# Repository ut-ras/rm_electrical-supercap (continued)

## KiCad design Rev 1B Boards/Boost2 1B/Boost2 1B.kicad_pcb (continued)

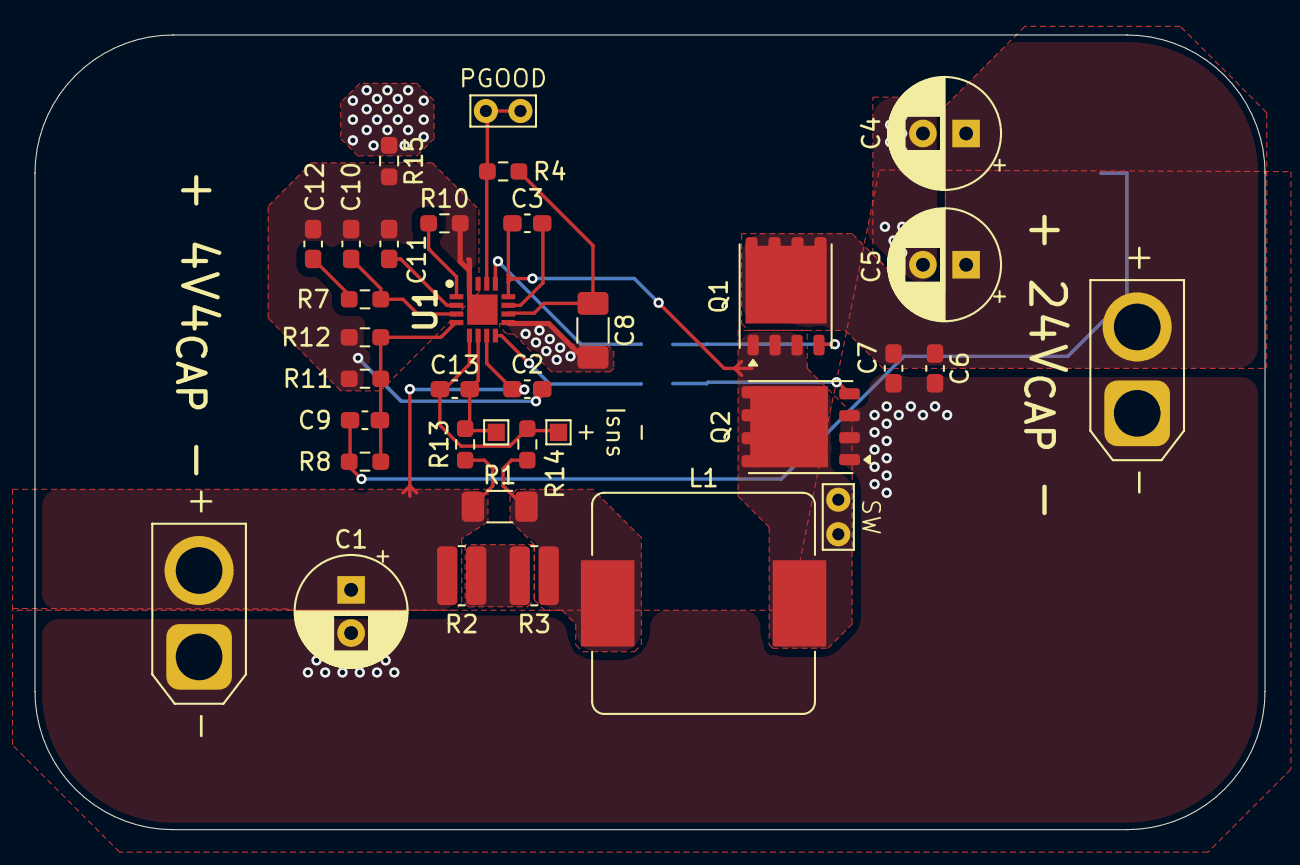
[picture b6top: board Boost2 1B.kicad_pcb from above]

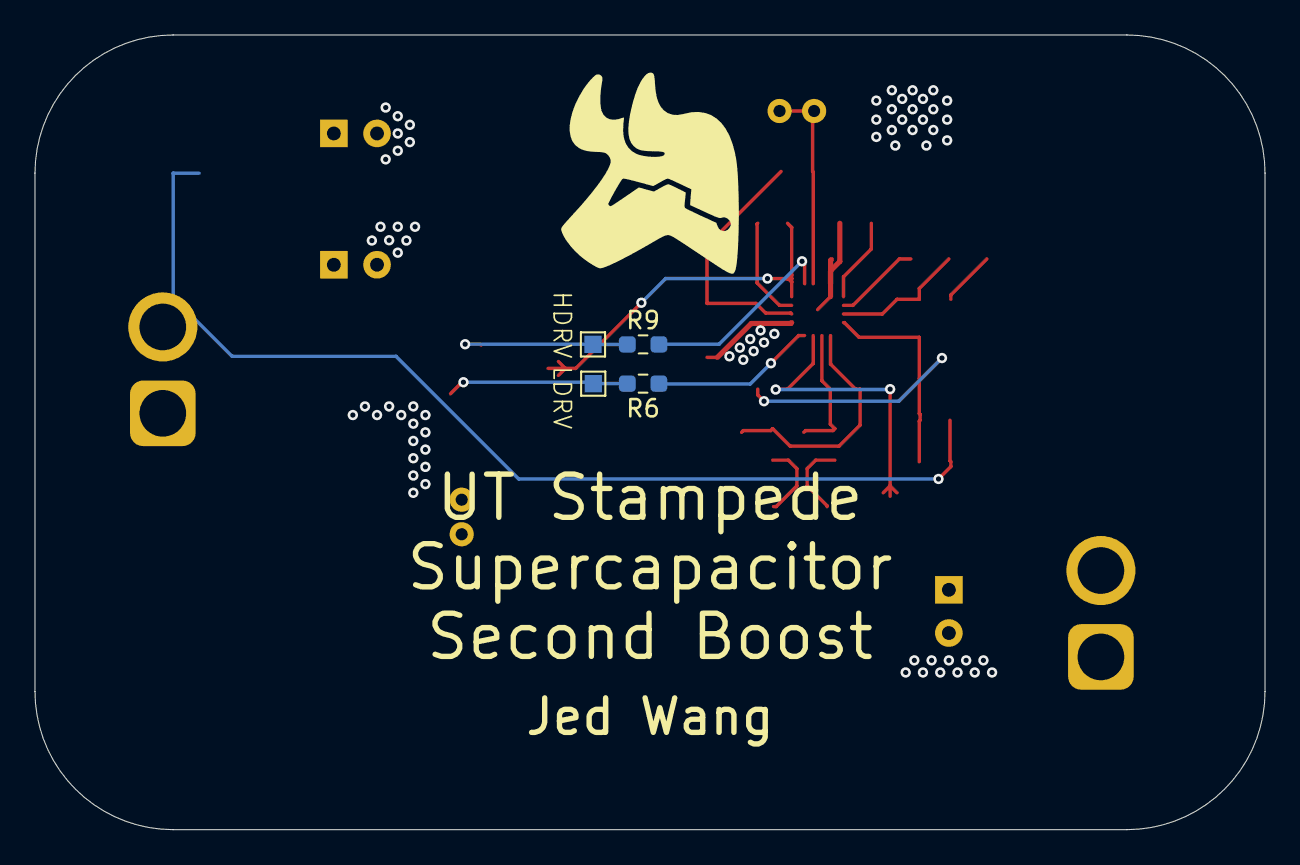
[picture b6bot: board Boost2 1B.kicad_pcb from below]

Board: 4 copper layers, 71.2 x 46.0 mm, 39 parts (4 on the bottom side), 21 nets.

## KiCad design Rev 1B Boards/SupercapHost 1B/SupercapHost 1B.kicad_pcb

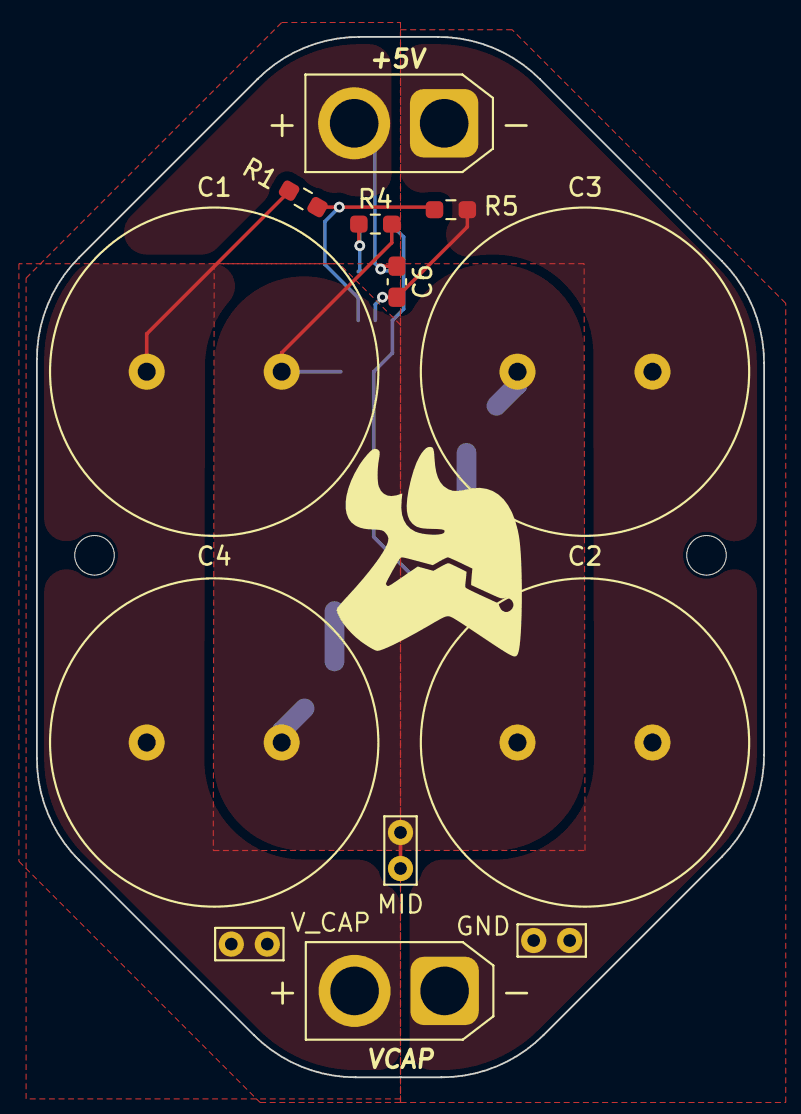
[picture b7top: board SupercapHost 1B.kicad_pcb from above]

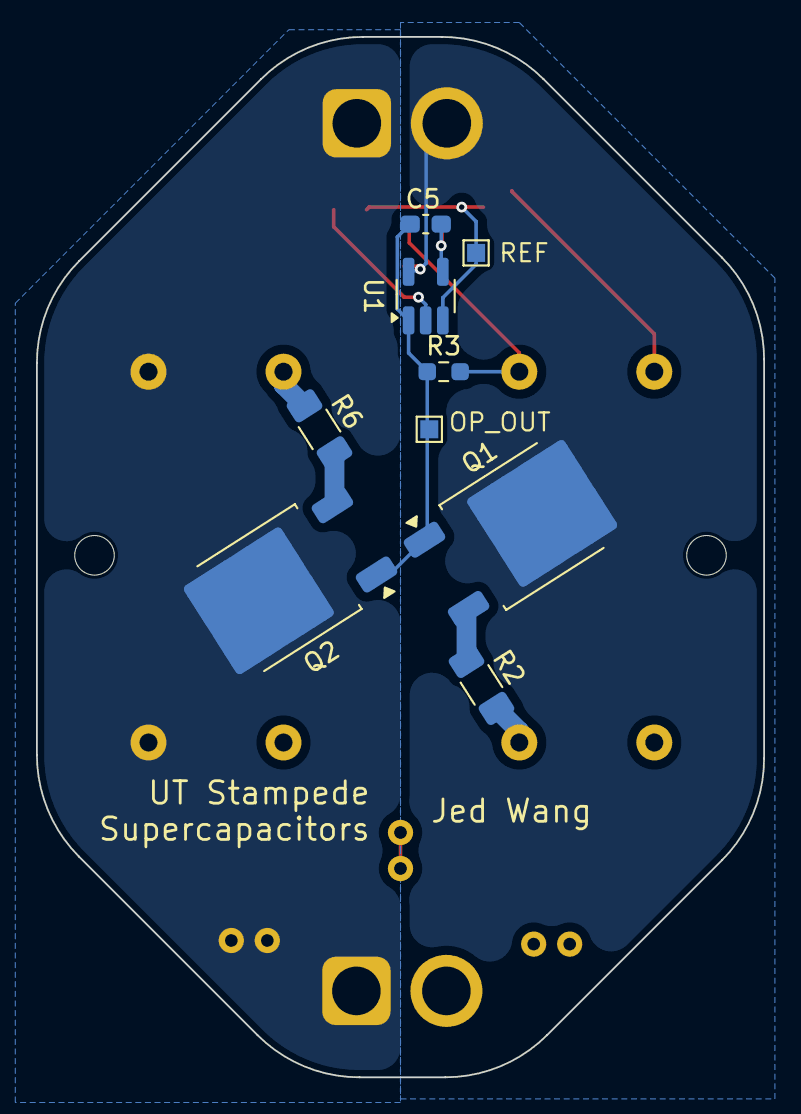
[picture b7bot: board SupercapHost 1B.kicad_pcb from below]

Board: 2 copper layers, 40.4 x 57.8 mm, 22 parts (9 on the bottom side), 9 nets.

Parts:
C1, C2, C3, C4: 110; C_Radial_D18.0mm_H35.5mm_P7.50mm
C5: 100p; C_0603_1608Metric_Pad1.08x0.95mm_HandSolder
C6: 0.1u; C_0603_1608Metric_Pad1.08x0.95mm_HandSolder
J1, J2: XT30_F; AMASS_XT30U-F_1x02_P5.0mm_Vertical
Q1: 2SCR587D3; TO-252-2
Q2: 2SAR587D3; TO-252-2
R1, R5: 1Meg; R_0603_1608Metric_Pad0.98x0.95mm_HandSolder
R2, R6: 0.1; R_1206_3216Metric_Pad1.30x1.75mm_HandSolder
R3, R4: 100; R_0603_1608Metric_Pad0.98x0.95mm_HandSolder
TP1, TP4: TP; TestPoint_Pad_1.0x1.0mm
TP2, TP3, TP5: TP; TestPoint_Bridge_Pitch2.0mm_Drill0.7mm
U1: TLV9301xDBV; SOT-23-5_HandSoldering

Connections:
/Supercapacitors/LOWER_R: Q2.3 (E), R6.2
/Supercapacitors/MID: C1.2, C2.2, C3.1, C4.1, R2.2, R3.2, R4.1, R6.1, TP3.1
/Supercapacitors/OP_OUT: C5.2, Q1.1 (B), Q2.1 (B), R3.1, TP1.1, U1.1
/Supercapacitors/REF: R1.2, R5.1, TP4.1, U1.3 (+)
/Supercapacitors/UPPER_R: Q1.3 (E), R2.1
/Supercapacitors/V-: C5.1, R4.2, U1.4 (-)
/Supercapacitors/V_{CAP}: C1.1, C2.1, J1.2, R1.1, TP2.1
/Supercapacitors/V_{CC}: C6.1, J2.2, Q1.2 (C), U1.5 (V+)
GND1: C3.2, C4.2, C6.2, J1.1, J2.1, Q2.2 (C), R5.2, TP5.1, U1.2 (V-)

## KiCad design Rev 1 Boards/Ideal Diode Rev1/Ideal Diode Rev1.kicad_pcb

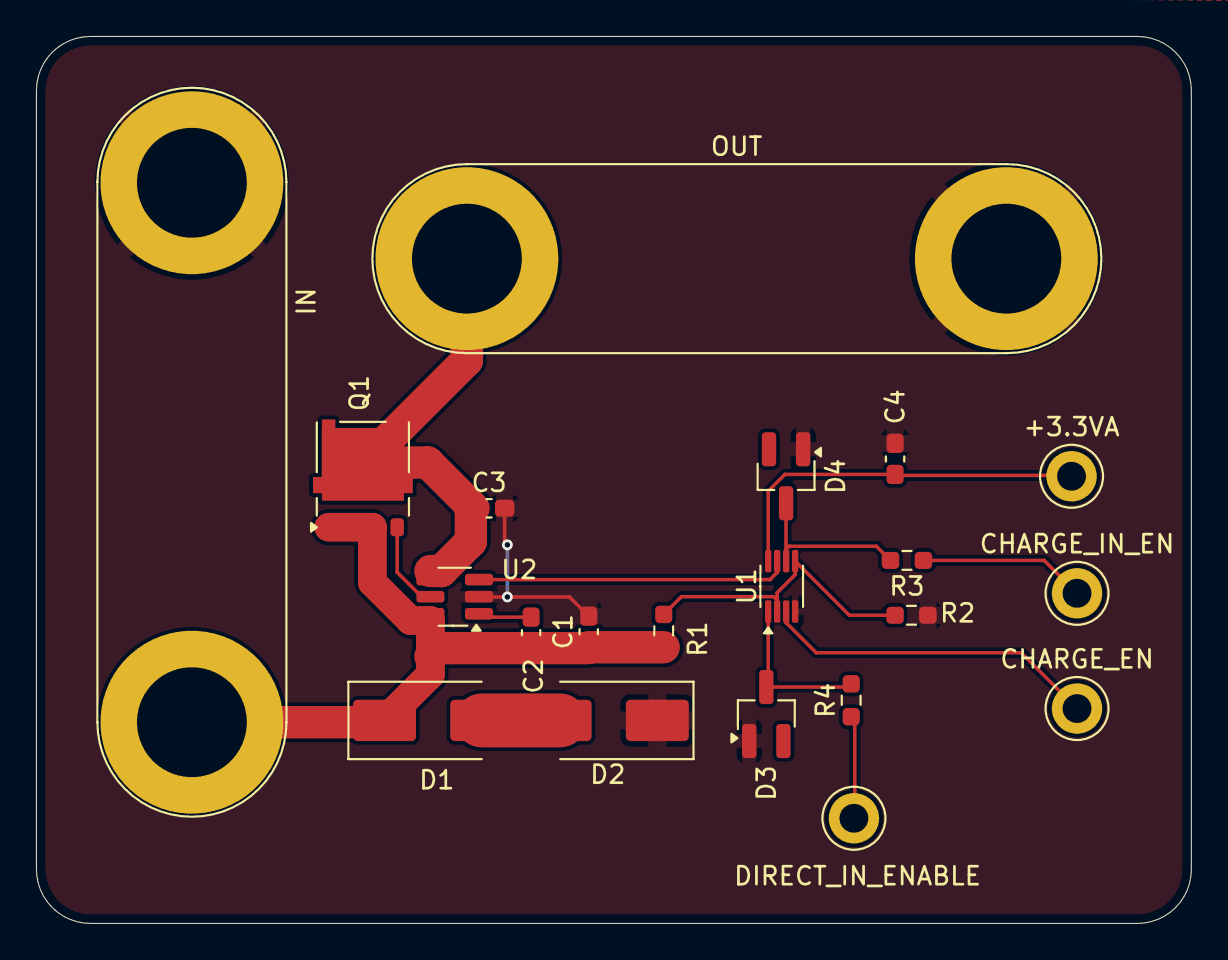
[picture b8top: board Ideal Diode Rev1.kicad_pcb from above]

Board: 2 copper layers, 64.2 x 49.3 mm, 21 parts (0 on the bottom side), 14 nets.

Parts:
+3.3VA: TestPoint; TestPoint_Keystone_5010-5014_Multipurpose
C1: 0.022u; C_0603_1608Metric_Pad1.08x0.95mm_HandSolder
C2, C4: 0.1u; C_0603_1608Metric_Pad1.08x0.95mm_HandSolder
C3: 47u; C_0603_1608Metric_Pad1.08x0.95mm_HandSolder
CHARGE_EN: TestPoint; TestPoint_Keystone_5010-5014_Multipurpose
CHARGE_IN_EN: TestPoint; TestPoint_Keystone_5010-5014_Multipurpose
D1: SMBJ58A; D_SMB_Handsoldering
D2: SMBJ26A; D_SMB_Handsoldering
D3, D4: BAT54; SOT-23_Handsoldering
DIRECT_IN_ENABLE: TestPoint; TestPoint_Keystone_5010-5014_Multipurpose
IN: Conn_01x02_Socket; Banana_Jack_2Pin
OUT: Conn_01x02_Socket; Banana_Jack_2Pin
Q1: NVMFS5C404NL; ONSemi_SO-8FL_488AA
R1: 91k; R_0603_1608Metric_Pad0.98x0.95mm_HandSolder
R2: 13k; R_0603_1608Metric_Pad0.98x0.95mm_HandSolder
R3, R4: 1k; R_0603_1608Metric_Pad0.98x0.95mm_HandSolder
U1: SN74LVC2G08; VSSOP-8_2.3x2mm_P0.5mm
U2: LM74700; SOT-23-6_Handsoldering

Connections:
+3.3VA: +3.3VA.1, C4.1, U1.8 (VCC)
/Ideal Diode/CHARGING_EN: CHARGE_EN.1, U1.3
/Ideal Diode/CHARGING_IEN: CHARGE_IN_EN.1, R3.1
/Ideal Diode/C_CLIP: D4.3 (K), R3.2, U1.6
/Ideal Diode/DIRECT_EN: U1.7, U2.3 (EN)
/Ideal Diode/DIRECT_IEN: DIRECT_IN_ENABLE.1, R4.1
/Ideal Diode/D_CLIP: D3.3 (K), R4.2, U1.1
/Ideal Diode/GATE: Q1.4 (G), U2.5 (GATE)
/Ideal Diode/IN: C1.1, C2.1, D1.1 (K), IN.1, Q1.1 (S), Q1.2 (S), Q1.3 (S), R1.1, U2.6 (ANODE)
/Ideal Diode/OUT: C3.1, OUT.1, Q1.5 (D), U2.4 (CATHODE)
/Ideal Diode/TVS_mid: D1.2 (A), D2.2 (A)
/Ideal Diode/VCAP: C2.2, U2.1 (VCAP)
/Ideal Diode/V_{ON}: R1.2, R2.1, U1.2, U1.5
GNDPWR: C1.2, C3.2, C4.2, D2.1 (K), D3.1 (A), D4.1 (A), IN.2, OUT.2, R2.2, U1.4 (GND), U2.2 (GND)

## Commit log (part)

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2024-10-18 Initial commit
    Creating project files
2024-10-18 Add schematic page properties
2024-10-18 Add subsheets
2024-10-20 Added some text in the subsheets to outline what needs to be added inside of each subsheet
2024-10-21 Added two more subsheets and updated all text inside
2024-10-25 Add note about synchronous boost/buck needed
2024-10-26 Added in & out data from each subsheet
    For more details, please contact @leftisttachyon on Discord
2024-11-16 Completed first version of housekeeping supplies
    +5V and +3V3 from mini PC +24V
2024-11-16 Adjust documentation
2024-11-22 added isense
2024-11-23 Selected an ideal diode
2024-11-23 Selected components for ideal diode and DACs
2024-11-24 Trying to do current sense but it's not fun
    canercanercnarennc
2024-11-24 Completed sense comparators
2024-12-07 Finish Dev board interface
    sorry morris
2024-12-07 Formatting in dev_interface
2024-12-07 flip
2024-12-07 Fix ground references
2024-12-07 last formatting change I promise
2024-12-07 Update library + update symbols
2024-12-07 Updating symbol library + passing some ERC tests
2024-12-07 Remove previous version of current sense
2024-12-07 Add input resistor divider to battery voltage ADC
    + renumbered components
2024-12-07 Add in voltage control for components
2024-12-07 Added proper peripherals to ideal diode controller
    also updated library
2024-12-07 Polish up ideal diode subsheet
    Made custom symbol for multipinned FET
2024-12-08 Finishing buck charger
2024-12-08 Define feedback networks
2024-12-08 Finish up buck
2024-12-08 Add global connectors
    Also realize I messed up the current sense
2024-12-08 attempting to fix comparators
    + global routing
2024-12-08 Reannotated
2024-12-09 Attempting to use just an opamp probably won't work
    Will use diff amp + schmitt trigger
2024-12-15 Adding new DC DC converter IC
2024-12-15 Complete redesign of housekeeping supplies
    Attached picture is for the design of the housekeeping supplies
2025-01-25 Reorganize block diagram
    Now with fewer wires crossing
2025-01-31 Ideating for diff amp
2025-02-01 Created new folder for SPICE simulations, created SPICE simulation for ideal diode controller
2025-02-01 Moving around things
2025-02-12 Updated sheet dates & added new subsheets for parts I forgot to include
2025-02-12 Normally open => closed
2025-02-15 Replaced buck converter for 3V3, 3V3A, 5V with AZ34063U
2025-02-15 Added -3V3
2025-02-15 Added schematic for first stage of boost converter
2025-02-15 Reorganized diagram so it's neater!
2025-02-21 Schematic review suggestions reflected (removed 4-way junctions, changed symbol)
2025-02-22 started safetydischarge
2025-02-22 Changed boost2
2025-02-22 Updated resistor/capacitor values for current sense and added corresponding Mouser part numbers
2025-02-22 Updated AND gate input circuits, added specs to diodes
2025-02-22 Replaced opamp with better one
2025-02-28 current Sense simulation
2025-02-28 Update boost 2
2025-03-01 Changed to GNDPWR for -3V3 step-down converter
2025-03-01 Redesigned stage 1 converter for clarity
2025-03-01 Reduced link size, added buck converter calculations excel sheet
2025-03-07 updated discharge subsheet
2025-03-08 Flip MOSFET for ideal diode controller
2025-03-08 Switched over to TI buck conveter
2025-03-08 To simulate buck, replace 22u with {L2} and 100u with {C3}
2025-03-17 Update current sense comparator resistor values
2025-03-20 Simulated + designed current sense circuitry
2025-03-20 Simplifying schematic with more same parts and fewer components
2025-03-20 Remove flavor text for validation
2025-03-20 Update simulations to match current sensor design
2025-03-21 Adjust housekeeping power supplies to remove output filter network
2025-03-21 Remove unnecessary files
    DON'T COMMIT THESE HUGE FILES TO GIT IN THE FUTURE!!!
2025-03-21 Updating discharge circuit to work with +24V power
2025-03-21 Renumber components
2025-03-21 Various mouser part changes
2025-03-21 Added project-level library
2025-03-22 Update library to checkout on submodule update
2025-03-22 IMPORTANT: .gitmodules points to KiCad_Library/supercap_components and symbol table points to KiCad_Library submodule for this project
2025-03-22 Configured fp library to point to local kicad_lib submodule
2025-03-24 Update project to KiCAD 9.0 + redo stage 1 schematic
2025-03-24 Redo boost converter (frist stage)
2025-03-28 Create Rev1 board projects + delete extraneous schematic file
2025-03-28 Add input buck subproject
2025-03-28 Add libraries to subprojects
2025-03-28 Correct symbol library path, renumber components
2025-03-29 Fix broken component links
2025-03-29 changed some simulation numbers and current sense capacitor
2025-03-29 Update symbol libraries and link footprint libraries
2025-03-29 added footprints to prepare for pcb layout
2025-03-29 fixed misallocation of footprint file
2025-04-04 Create last two rev1 test boards
2025-04-04 assigned footprints, mouser part numbers, and datasheets for passive components
2025-04-04 Rename projects to be more descriptive
2025-04-04 Add new components to housekeeping power supply
2025-04-04 beginning layout work for housekeeping pcb
2025-04-04 update library version
2025-04-05 Change up capacitor values and footprints to reduce the number of bulk caps needed
2025-04-05 current sense PCB layout
2025-04-11 added mouser part numbers and corresponding datasheets/footprints for components
2025-04-11 began pcb layout ofr housekeeping
2025-04-13 Created rudimentary component placements for Housekeeping PCB layout Pending approval from Jed before putting down traces
2025-04-14 Created preliminary layout for Housekeeping PCB with traces added. Still needs review + connection of nets to ground fills.
2025-04-14 added traces and pours for housekeeping pcb layout
2025-04-14 Add labels for nets
2025-04-14 Updated Housekeeping PCB layout after review with Jed
2025-04-18 restore broken current sense schematic
2025-04-18 current sense tweaks
2025-04-18 Changed fill types for SW nets and added silkscreen labels for banana connectors
2025-04-18 fixed DRC violations with housekeeping PCB layout
2025-04-19 address current sense review issues
2025-04-19 Layout iteration 1 for the input buck
2025-04-19 Created preliminary board layout for dev board interface pcb, pending review by Jed
2025-04-25 modified tracks
2025-04-25 implemented dev board interface review suggestions as per morris
2025-04-25 review 2 revisions
2025-04-25 Did partial fixes according to round 2 review of dev board interface as per jed
2025-04-26 reworked dev board interface pcb layout to put all ICs on the same side as per jed review
2025-04-26 began ideal diode layout
2025-04-26 Minor changes
    Still need to replace the inductor footprint with the correct one
2025-04-26 Finished layout
    Still need to replace the footprint for the inductor
2025-04-26 Added labels
2025-04-26 More labels
2025-04-26 Update KiCad_Library
2025-05-07 Completed stage 2 schematic
    + added SPICE models for all the custom components
    + renumbered components
    + updated library with stage 2 symbols
2025-05-08 Add specific .gitignore for sims
2025-05-08 Attempt to design & simulate the part 2 boost
    Doesnt' seem to work for some reason
2025-05-08 Fix path for .gitignore
2025-05-08 Theorycrafting better load sharing solutions
2025-05-10 Finalize load sharing schematic
    >=97% efficiency with constant current load
2025-05-10 Minor tweaks
2025-05-10 Removed -30V source, still functioning
2025-05-11 Testing out different op amps to see how low we can push the power consumption
2025-05-11 Add scratch work
2025-05-11 Rename to more descriptive file names
2025-05-11 Add missing opamp symbol
2025-05-12 Completed designing both load balancing and buck enable circuits
2025-05-12 Fix fills
2025-05-13 ideal diode review 1 updates
2025-05-13 ideal diode review 1 changes
2025-05-13 Implement SPICE'd circuits in KiCAD
2025-05-13 Forgot one label
2025-05-13 Completed block diagram
2025-05-13 Add note for self
2025-05-13 Vastly simplified charge EN circuit
2025-05-13 Redesign housekeeping supplies
2025-05-13 Update Mouser part numbers
    Some resistors will be wrong, please check
2025-05-13 Remove Mouser part number fields from visibility
2025-05-13 Correct text removal
2025-05-14 review 1 ideal diode changes
2025-05-14 Properly spec 30V output
2025-05-14 Update .gitignore for Excel
2025-05-15 Tuned circuits & adjusted values
    Changed footprints for some circuits to consolidate components
2025-05-15 Move design sheets to the design folder
2025-05-15 Change .xls to .xlsx
2025-05-15 Considering using a different IC for 1st stage
2025-05-15 Save designs + update library
2025-05-15 Add another design spreadsheet
2025-05-16 Redesigning output boosts to be more efficient albeit with less current capacity
    idk what I changed with the schematics lol
2025-05-17 Successful design completed!
    Much more stable current sensing control
2025-05-17 Update SPICE footprints to make them easier to drop in replace in LTSpice
2025-05-17 Try using cheaper op-amps
2025-05-17 Revert "Try using cheaper op-amps"
    This reverts commit 3967edb0c8b95dc5b95d6bf4fb9c46c6938682c0.
2025-05-17 Transfer new design to schematic
2025-05-17 Find suitable op-amp for buffer in current sense
2025-05-18 Up charging current to 6A
2025-05-19 ideal diode review 3 changes
2025-05-19 Add supercaps subsheets
2025-05-19 Adding simulation for charging & balancing
2025-05-19 Finalize balancing circuit
    Looks pretty stable to me
2025-05-19 Adjust values for better feedback
2025-05-19 Updating buck converter to work with new 2S2P supercap stackup
2025-05-19 Various schematic touchups
2025-05-19 Reannotate schematic
2025-05-20 Finalized design !!!
2025-05-20 Remove autosaves
2025-05-20 Various touchups
2025-05-20 idk what I even changed lol
2025-05-20 Selected BJTs for the supercap balancing circuitry
2025-05-20 Reimplement +5V to supply 3A
2025-05-20 Adjusted some things + changed discharge to have a smaller time constant
2025-05-20 Renumbering components
2025-05-22 Add voltage ratings to capacitors & respec caps to not explode
2025-05-22 Sourcing various parts
2025-05-23 Specc'd all components + started creating rev 1b boards
2025-05-23 Test manufacturing
2025-05-23 Remove old housekeeping 1B rev for panelled PCB
2025-05-23 Created seperate boards for supercap
2025-05-24 Add test points to all subsheets
2025-05-24 Renumbered components for rev 1b layout
2025-05-24 Added local libraries (KiCAD_Library)
2025-05-24 Begin layout
    Completed ideal diode layout
2025-05-25 Add choice to limit minimum gate voltage to avoid maximum VGS violations
2025-05-25 Add documentation to isense sheet
    Also fiddle with simulations
2025-05-25 Re-enable BOM generation for supercap host board
2025-05-25 Completed preliminary layout
2025-05-25 Update manufacturing capabilities
2025-05-25 More layout
2025-05-25 Complete dev board interface layout
2025-05-25 Completed layout for input buck test board
2025-05-26 Add thermistor to BOM
2025-05-26 Polish input buck test board
2025-05-26 Update PCB to fix ERC breaks
2025-05-26 Save dev interface subsheet
2025-05-26 Placed footprints for boost stage 1 layout
2025-05-26 Completed first draft of layout
2025-05-26 Adjustments + tons of vias
2025-05-26 Completed Boost stage 1 layout
2025-05-26 Completed layout of supercap host board
2025-05-26 Complete touchups of supercap host board
2025-05-26 Create Housekeeping power supply test board
2025-05-26 Fix DRC issues
2025-05-26 Completed Housekeeping layout
2025-05-26 Add input filter to Boost 2
2025-05-26 Start boost 2 layout
2025-05-26 Update component library
2025-05-27 Complete boost2 layout
2025-05-27 Label boost2 board
2025-05-27 Add dimensions + round corners
2025-05-28 Complete routing for current sense test board
2025-05-28 Add labels + more test points
2025-05-28 Adjust one pour
2025-05-28 Adjust all PCBs and resize boards to be cheaper to order from JLCPCB
    Also changed connector pinout to reflect silkscreen
2025-05-29 Replace most banana jacks with XT connectors
    + update library
2025-06-15 Update feedback to 100pF instead of 1000pF
